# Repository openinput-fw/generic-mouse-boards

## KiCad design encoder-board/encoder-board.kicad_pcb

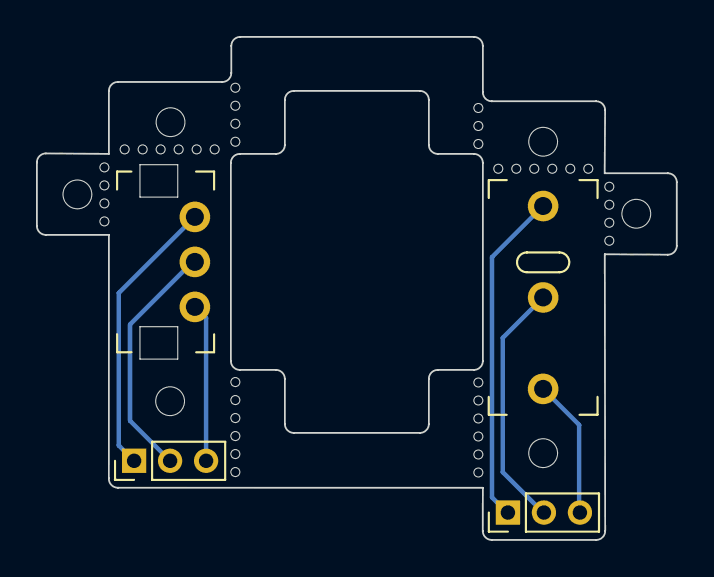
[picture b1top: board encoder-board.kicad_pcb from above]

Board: 4 copper layers, 35.5 x 27.9 mm, 4 parts (0 on the bottom side), 6 nets.

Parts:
J1: Enc; PinHeader_1x03_P2.00mm_Vertical
J2: SW; PinHeader_1x03_P2.00mm_Vertical
SW1: Rotary_Encoder; Encoder
SW2: SW_SPDT; Generic

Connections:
/ENC_A: J1.3, SW1.A
/ENC_B: J1.2, SW1.B
/EN_C: J1.1, SW1.C
/SW_C: J2.1, SW2.1 (B)
/SW_NC: J2.3, SW2.3 (A)
/SW_NO: J2.2, SW2.2 (C)

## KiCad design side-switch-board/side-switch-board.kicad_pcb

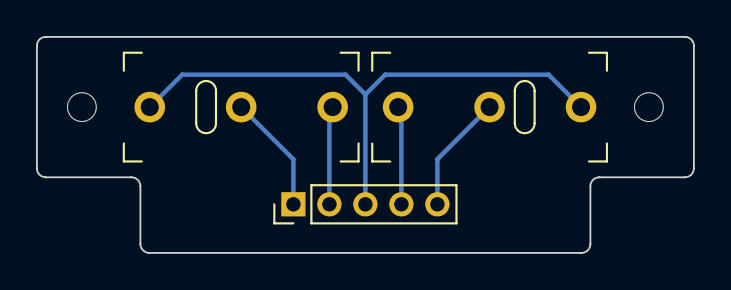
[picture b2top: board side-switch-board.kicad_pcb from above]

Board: 4 copper layers, 36.5 x 12.0 mm, 3 parts (0 on the bottom side), 5 nets.

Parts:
J0: Side; PinHeader_1x05_P2.00mm_Vertical
SW1, SW2: SW_SPDT; Generic

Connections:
/SW1_C: J0.3, SW1.1 (B), SW2.1 (B)
/SW1_NC: J0.2, SW1.3 (A)
/SW1_NO: J0.1, SW1.2 (C)
/SW2_NC: J0.4, SW2.3 (A)
/SW2_NO: J0.5, SW2.2 (C)

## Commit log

2021-04-30 all: imported from big-sammy project

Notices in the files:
encoder-board/encoder-board.kicad_pcb:
This source describes Open Hardware and is licensed under the CERN-OHL-Pv2
Copyright (c) Rafael Silva
